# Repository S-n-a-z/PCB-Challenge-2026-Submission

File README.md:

# PCB Challenge 2026

My working layout for the [Fleming Society PCB Challenge](https://github.com/Fleming-Society/PCB-Challenge-2026).

This branch is not ready for submission. There are still **18 unconnected items**, along with two via-placement issues and symbol and footprint mismatches to resolve before the final check.

## Current layout

| Item | Result |
| --- | --- |
| Board outline | 66.7 × 67.2 mm |
| Bounding-box area | 4,482.24 mm² |
| Components | 164 |
| Copper layers | Four |
| Board thickness | 1.6 mm |
| Unconnected items | 18 |
| Other standard DRC errors | 0 |
| DRC warnings | 16 |
| Additional schematic-parity findings | 39 |

This checkpoint includes the manual routing progress and further data, enable and read-pointer connections. The remaining work is listed, with coordinates, in [Remaining connections](REMAINING_CONNECTIONS.md). No claim is made that this is ready for manufacture or a completed challenge entry.

The inner layers carry ground and 3V3 pours as well as some signal routes. The control routes on the ground layer stay outside the USB reference area. A separate check of the filled zone found no gaps beneath either main USB trace.

## Opening the project

Open `pcb_challenge_final.kicad_pro` in KiCad 10. The supplied custom footprints are included under `footprints/` and linked through `fp-lib-table`.

The schematic comes from the organisers' corrected files at commit [`8f8f4e2`](https://github.com/Fleming-Society/PCB-Challenge-2026/commit/8f8f4e241fe25e6dbe64b1d4abbda95879012cd6). The layout retains their footprint geometry, including the supplied ESP32 footprint that differs from the installed KiCad library.

## Checks and remaining work

The [DRC report](checks/drc.json) was generated with KiCad 10.0.7. It includes the open connections and the separate schematic-parity findings. The source has inconsistencies around the reset switch, unused symbol pins and USB shield numbering; these still need reviewing. The shield pads are named `SH` in the footprint and `S1` in the symbol.

The [layout audit](checks/layout-audit.json) checks via placement and the USB reference plane. Two existing vias on `b2` and `b3` overlap U10's courtyard; the `b2` via is also in a pad. Those still need moving. The check found no gaps beneath the main USB traces. The same-layer IC courtyard restriction still needs a full review.

The design rules use a 0.15 mm minimum track width, 0.12 mm clearance, 0.3 mm copper-to-edge clearance and 0.6/0.3 mm vias with a 0.15 mm annular ring. Zero other standard DRC errors does not mean the board is finished: open connections and the separate parity and challenge-rule findings remain.

The logic deduction is kept in the local form notes rather than this public repository. The [submission checklist](SUBMISSION_CHECKLIST.md) records what is still outstanding.

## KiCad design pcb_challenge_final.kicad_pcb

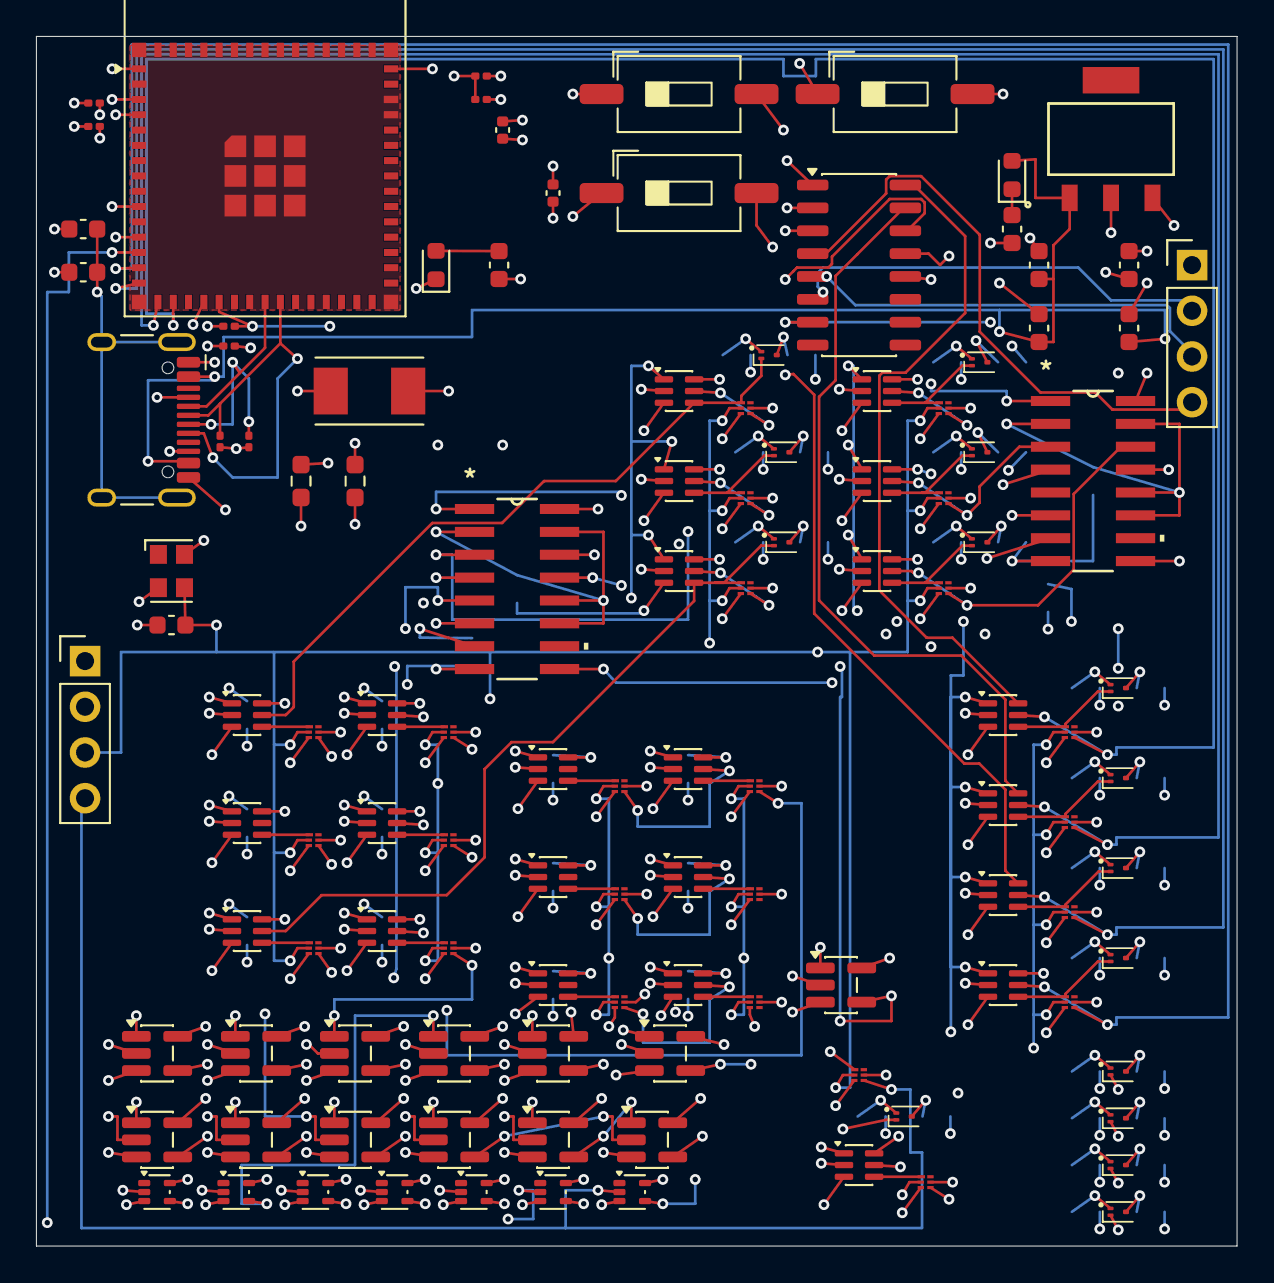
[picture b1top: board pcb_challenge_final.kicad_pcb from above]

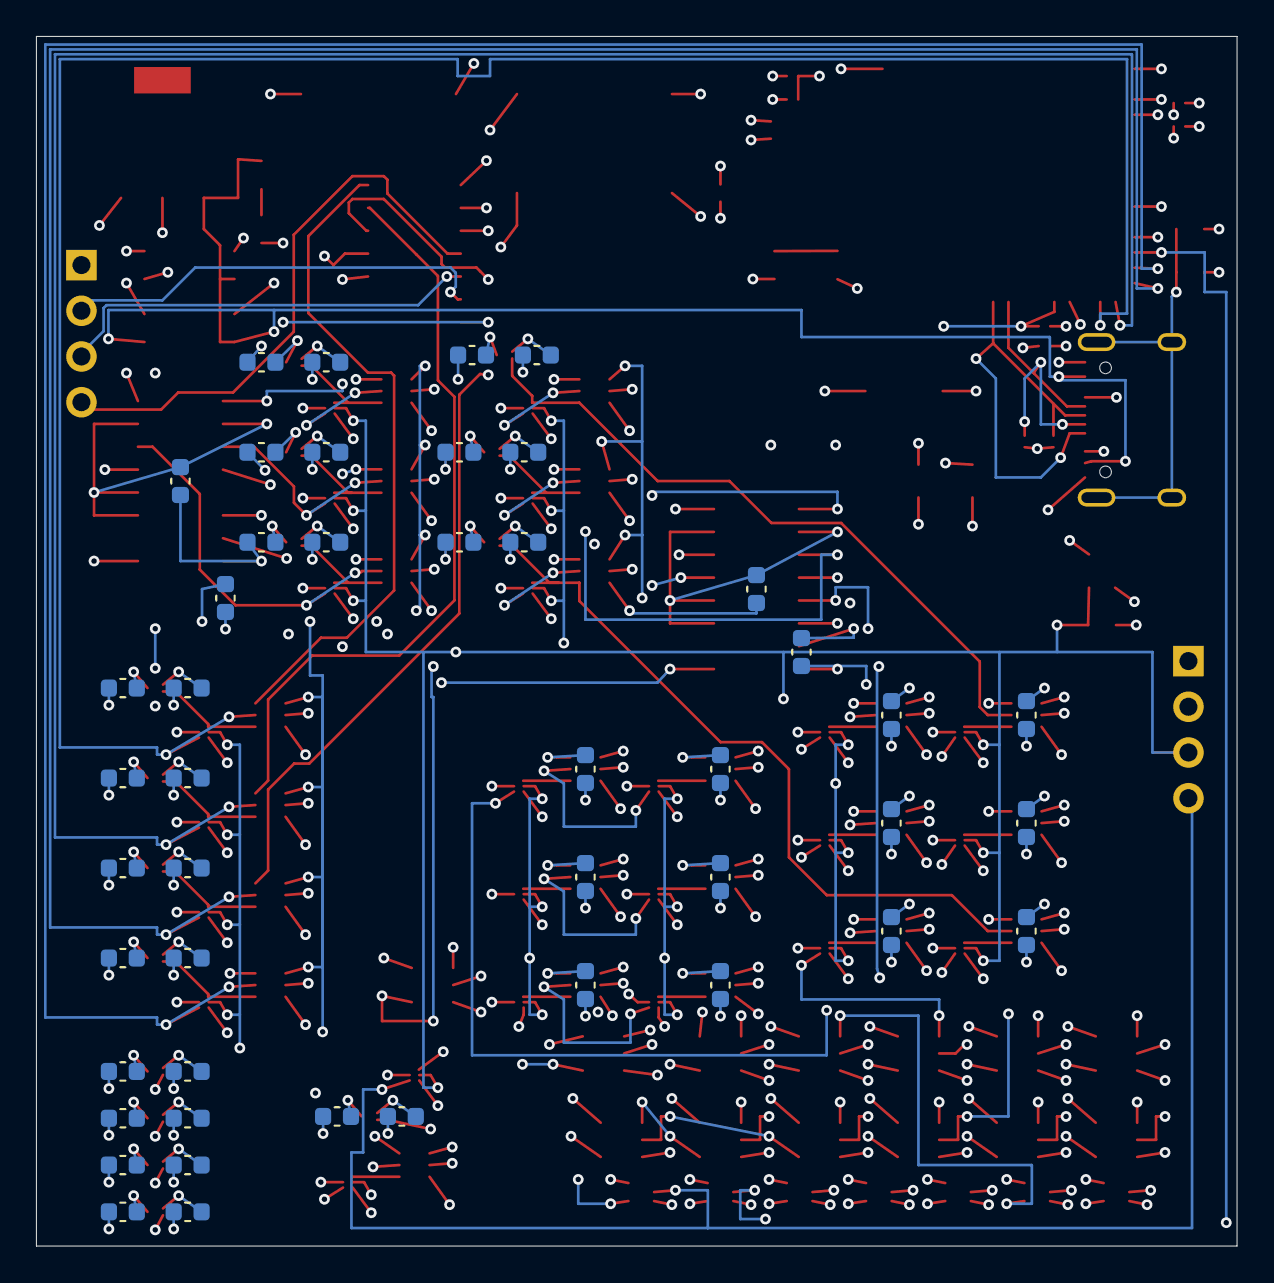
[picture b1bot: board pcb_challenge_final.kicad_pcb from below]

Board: 4 copper layers, 66.7 x 67.2 mm, 164 parts (46 on the bottom side), 134 nets.

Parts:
C1, C7: 22uF; C_0201_0603Metric
C2, C8: 0.1uF; C_0201_0603Metric
C3, C4: 12pF; C_0201_0603Metric
C5, C6: 22pF; C_0201_0603Metric
C9: 100nF; C_0402_1005Metric
C13, C14: 1uF; C_0603_1608Metric
C15, C20: 10uF; C_0603_1608Metric
D1: BLED; LED_0603_1608Metric
GREEN_LED1: LED; LED_0603_1608Metric
J3: USB_C_Receptacle_HCTL_HC-TYPE-C-16P-01A
J4, J5: Conn_01x04_Pin; PinHeader_1x04_P2.54mm_Vertical
Q15, Q16, Q17, Q18, Q19, Q20, Q21, Q22, Q23, Q24, Q25, Q26, Q27, Q28, Q29: Q_Dual_NPN_PNP_B1E2B2C2E1C1; SOT-1123
R1: 10k; C_0402_1005Metric
R3: 1k; C_0603_1608Metric
R4: 330; C_0603_1608Metric
R6, R24: 1M; C_0603_1608Metric
R7, R21, R22, R23, R25, R26, R27, R28, R29, R30, R31, R32, R33, R34, R35, R36, R37, R38, R39, R40, R41, R42, R43, R44, R45, R46, R47, R48, R49, R50, R51, R52, R53, R54, R55, R56, R57, R58, R59, R61, R62, R63, R64, R65, R66, R67, R68: 10k; C_0603_1608Metric
R15, R20: 5.1k; R_0603_1608Metric_Pad0.98x0.95mm_HandSolder
SW1, SW2, SW3: SW_Push; SW_DIP_SPSTx01_Slide_6.7x4.1mm_W8.61mm_P2.54mm_LowProfile
U1, U4, U5, U6, U7, U8, U17, U19, U20, U33, U34, U37, U38, U45, U46, U47, U48, U49, U50, U65, U66, U67, U68, U69: 74AUP1G80; XSON6_SOT1115_NEX
U3, U18, U52, U55, U56, U60: 74AHC1G86; SC-74A-5_1.55x2.9mm_P0.95mm
U9: TC1262-25; SOT-223_3MC_MCH
U10: NMUX1308BQ; SO-16_3.9x9.9mm_P1.27mm
U11, U12, U13, U14, U15, U16, U29, U30, U31, U32, U35, U36, U39, U40, U41, U42, U43, U44, U64, U70, U71, U72, U73: NMUX1308BQ; SOT-363_SC-70-6
U21, U23, U27, U51, U59, U62, U63: 74LV1T08GV; SC-74A-5_1.55x2.9mm_P0.95mm
U22, U28: CD74HC283M96; D16
U24, U26, U53, U54, U57, U58, U61: 74LVC1GU04DRL; SOT-553
U25: ESP32-S3-MINI-1; ESP32-S2-MINI-1
Y1: 32.768KHz; Crystal_SMD_Abracon_ABM7-2Pin_6.0x3.5mm
Y2: KC2520Z; Oscillator_SMD_Kyocera_KC2520Z-4Pin_2.5x2.0mm

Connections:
+3.3V: C1.1, C2.1, C14.1, R1.1, R3.1, U1.5 (VCC), U3.5 (VCC), U4.5 (VCC), U5.5 (VCC), U6.5 (VCC), U7.5 (VCC), U8.5 (VCC), U9.3 (VO), U10.1 (V_{CC}), U11.2 (V_{CC}), U12.2 (V_{CC}), U13.2 (V_{CC}), U14.2 (V_{CC}), U15.2 (V_{CC}), U16.2 (V_{CC}), U17.5 (VCC), U18.5 (VCC), U19.5 (VCC), U20.5 (VCC), U21.5 (VCC), U22.6 (B0), U22.16 (VCC), U23.5 (VCC), U24.5 (+), U25.3 (3V3), U26.5 (+), U27.5 (VCC), U28.6 (B0), U28.16 (VCC), U29.2 (V_{CC}), U30.2 (V_{CC}), U31.2 (V_{CC}), U32.2 (V_{CC}), U33.5 (VCC), U34.5 (VCC), U35.2 (V_{CC}), U36.2 (V_{CC}), U37.5 (VCC), U38.5 (VCC), U39.2 (V_{CC}), U40.2 (V_{CC}), U41.2 (V_{CC}), U42.2 (V_{CC}), U43.2 (V_{CC}), U44.2 (V_{CC}), U45.5 (VCC), U46.5 (VCC), U47.5 (VCC), U48.5 (VCC), U49.5 (VCC), U50.5 (VCC), U51.5 (VCC), U52.5 (VCC), U53.5 (+), U54.5 (+), U55.5 (VCC), U56.5 (VCC), U57.5 (+), U58.5 (+), U59.5 (VCC), U60.5 (VCC), U61.5 (+), U62.5 (VCC), U63.5 (VCC), U64.2 (V_{CC}), U64.6 (Y1), U65.5 (VCC), U66.5 (VCC), U67.5 (VCC), U68.5 (VCC), U69.5 (VCC), U70.2 (V_{CC}), U71.2 (V_{CC}), U72.2 (V_{CC}), U73.2 (V_{CC}), Y2.4 (VCC)
+5V: C13.1, C15.1, C20.1, GREEN_LED1.2 (A), J3.A4 (VBUS), J3.A9 (VBUS), J3.B4 (VBUS), J3.B9 (VBUS), U9.1 (VI)
???: J5.4, U1.4 (~Q), U26.2
COUT: U22.9 (COUT), U28.9 (COUT)
GND: C1.2, C2.2, C3.1, C4.1, C5.2, C6.2, C7.2, C8.2, C9.2, C13.2, C14.2, C15.2, C20.2, D1.1 (K), J3.A1 (GND), J3.A12 (GND), J3.B1 (GND), J3.B12 (GND), R4.1, R6.1, R7.1, R15.1, R20.2, R21.1, R22.1, R23.1, R24.1, R25.1, R26.1, R27.1, R28.1, R29.1, R30.1, R31.1, R32.1, R33.1, R34.1, R35.1, R36.1, R37.1, R38.1, R39.1, R40.1, R41.1, R42.1, R43.1, R44.1, R45.1, R46.1, R47.1, R48.1, R49.1, R50.1, R51.1, R52.1, R53.1, R54.1, R55.1, R56.1, R57.1, R58.1, R59.1, R61.1, R62.1, R63.1, R64.1, R65.1, R66.1, R67.1, R68.1, SW1.1, SW2.1, SW3.2, U1.3 (GND), U3.3 (GND), U4.3 (GND), U5.3 (GND), U6.3 (GND), U7.3 (GND), U8.3 (GND), U9.2 (GND), U10.2 (GND), U11.3 (GND), U12.3 (GND), U13.3 (GND), U14.3 (GND), U15.3 (GND), U16.3 (GND), U17.3 (GND), U18.3 (GND), U19.3 (GND), U20.3 (GND), U21.3 (GND), U22.8 (GND), U23.3 (GND), U24.3 (-), U25.1 (GND), U26.3 (-), U27.3 (GND), U28.8 (GND), U29.3 (GND), U30.3 (GND), U31.3 (GND), U32.3 (GND), U33.3 (GND), U34.3 (GND), U35.3 (GND), U36.3 (GND), U37.3 (GND), U38.3 (GND), U39.3 (GND), U40.3 (GND), U41.3 (GND), U42.3 (GND), U43.3 (GND), U44.3 (GND), U45.3 (GND), U46.3 (GND), U47.3 (GND), U48.3 (GND), U49.3 (GND), U50.3 (GND), U51.3 (GND), U52.3 (GND), U53.3 (-), U54.3 (-), U55.3 (GND), U56.3 (GND), U57.3 (-), U58.3 (-), U59.3 (GND), U60.3 (GND), U61.3 (-), U62.3 (GND), U63.3 (GND), U64.3 (GND), U65.3 (GND), U66.3 (GND), U67.3 (GND), U68.3 (GND), U69.3 (GND), U70.3 (GND), U71.3 (GND), U72.3 (GND), U73.3 (GND), Y2.2 (GND)
IO6: U6.2 (C), U7.2 (C), U8.2 (C), U25.10 (IO6), U45.2 (C), U46.2 (C), U47.2 (C), U48.2 (C), U49.2 (C), U50.2 (C), U65.2 (C), U66.2 (C), U67.2 (C), U68.2 (C), U69.2 (C)
IO7: U21.2 (A), U25.11 (IO7)
IO8: Q18.1 (B1), Q19.1 (B1), Q20.1 (B1), Q24.1 (B1), Q25.1 (B1), Q26.1 (B1), Q27.1 (B1), R35.2, R37.2, R39.2, R61.2, R63.2, R65.2, R67.2, U25.12 (IO8), U39.1 (S0), U40.1 (S0), U41.1 (S0), U42.1 (S0), U43.1 (S0), U44.1 (S0), U64.1 (S0)
IO9: U24.2, U25.13 (IO9), U65.4 (~Q)
IO10: U25.14 (IO10), U69.4 (~Q), U73.5 (Y0)
IO11: U25.15 (IO11), U68.4 (~Q), U70.5 (Y0)
IO12: U25.16 (IO12), U67.4 (~Q), U71.5 (Y0)
IO13: U25.17 (IO13), U66.4 (~Q), U72.5 (Y0)
unnamed: D1.2 (A), R3.2
unnamed: GREEN_LED1.1 (K), R4.2
unnamed: J3.A5 (CC1), R20.1
unnamed: J3.B5 (CC2), R15.2
unnamed: J3.SH, R6.2, R24.2
unnamed: Q15.3 (E1), R30.2
unnamed: Q16.2 (C1), U1.1 (D), U27.4 (Y)
unnamed: Q16.3 (E1), R32.2
unnamed: Q17.3 (E1), R28.2
unnamed: Q18.3 (E1), R40.2
unnamed: Q19.3 (E1), R38.2
unnamed: Q20.3 (E1), R36.2
unnamed: Q21.3 (E1), R44.2
unnamed: Q22.3 (E1), R45.2
unnamed: Q23.3 (E1), R46.2
unnamed: Q24.2 (C1), U66.1 (D), U72.4 (Out)
unnamed: Q24.3 (E1), R62.2
unnamed: Q25.2 (C1), U67.1 (D), U71.4 (Out)
unnamed: Q25.3 (E1), R64.2
unnamed: Q26.2 (C1), U68.1 (D), U70.4 (Out)
unnamed: Q26.3 (E1), R66.2
unnamed: Q27.2 (C1), U69.1 (D), U73.4 (Out)
unnamed: Q27.3 (E1), R68.2
unnamed: Q28.3 (E1), R26.2
unnamed: Q29.3 (E1), R22.2
unnamed: U18.4, U54.2
unnamed: U21.1 (B), U24.4
unnamed: R33.2, U22.2 (B1), U22.11 (B3), U22.12 (A3), U22.15 (B2)
unnamed: R25.2, U22.7 (CIN)
unnamed: U23.1 (B), U26.4
unnamed: C7.1, C8.1, R1.2, SW3.1, U25.45 (EN)
unnamed: U25.2 (GND), U25.42 (GND), U25.43 (GND), U25.46 (GND), U25.47 (GND), U25.48 (GND), U25.49 (GND), U25.50 (GND), U25.51 (GND), U25.52 (GND), U25.53 (GND), U25.54 (GND), U25.55 (GND), U25.56 (GND), U25.57 (GND), U25.58 (GND), U25.59 (GND), U25.60 (GND), U25.61 (GND), U25.62 (GND), U25.63 (GND), U25.64 (GND), U25.65 (GND)
unnamed: SW1.2, U25.4 (IO0)
unnamed: C3.2, U25.19 (IO15), Y1.2
unnamed: C4.2, U25.20 (IO16), Y1.1
unnamed: U3.4, U27.2 (A)
unnamed: U27.1 (B), U51.4 (Y)
unnamed: R47.2, U28.2 (B1), U28.11 (B3), U28.12 (A3), U28.15 (B2)
unnamed: R34.2, U28.7 (CIN)
unnamed: U4.1 (D), U29.4 (Out)
unnamed: R48.2, U29.6 (Y1)
unnamed: U5.1 (D), U30.4 (Out)
unnamed: U4.4 (~Q), U30.5 (Y0)
unnamed: R49.2, U30.6 (Y1)
unnamed: U31.4 (Out), U33.1 (D)
unnamed: R50.2, U31.6 (Y1)
unnamed: U32.4 (Out), U34.1 (D)
unnamed: U32.5 (Y0), U33.4 (~Q)
unnamed: R51.2, U32.6 (Y1)
unnamed: U35.4 (Out), U37.1 (D)
unnamed: R52.2, U35.6 (Y1)
unnamed: U36.4 (Out), U38.1 (D)
unnamed: U36.5 (Y0), U37.4 (~Q)
unnamed: R53.2, U36.6 (Y1)
unnamed: U39.4 (Out), U45.1 (D)
unnamed: R54.2, U39.6 (Y1)
unnamed: U40.4 (Out), U46.1 (D)
unnamed: R55.2, U40.6 (Y1)
unnamed: U41.4 (Out), U47.1 (D)
unnamed: R56.2, U41.6 (Y1)
unnamed: U42.4 (Out), U48.1 (D)
unnamed: U42.5 (Y0), U45.4 (~Q)
unnamed: R57.2, U42.6 (Y1)
unnamed: U43.4 (Out), U49.1 (D)
unnamed: U43.5 (Y0), U46.4 (~Q)
unnamed: R58.2, U43.6 (Y1)
unnamed: U44.4 (Out), U50.1 (D)
unnamed: U44.5 (Y0), U47.4 (~Q)
unnamed: R59.2, U44.6 (Y1)
unnamed: U51.2 (A), U54.4
unnamed: U51.1 (B), U53.4
unnamed: U52.4, U53.2
unnamed: U55.4, U57.2
unnamed: U56.4, U58.2
unnamed: U57.4, U59.2 (A)
unnamed: U58.4, U59.1 (B), U62.2 (A)
unnamed: U59.4 (Y), U63.2 (A)
unnamed: U60.4, U61.2
unnamed: U61.4, U62.1 (B)
unnamed: U62.4 (Y), U63.1 (B)
unnamed: U63.4 (Y), U64.5 (Y0)
unnamed: U64.4 (Out), U65.1 (D)
R_en: U10.12 (EN), U14.1 (S0), U15.1 (S0), U16.1 (S0), U23.4 (Y)
USB_D+: C5.1, J3.A6 (D+), J3.B6 (D+), U25.24 (USB_D+)
USB_D-: C6.1, J3.A7 (D-), J3.B7 (D-), U25.23 (USB_D-)
b1: J4.4, Q29.2 (C1), U10.4 (in1)
b2: J4.3, Q28.2 (C1), U10.5 (in2)
b3: J4.2, Q17.2 (C1), U10.6 (in3)
b4: J4.1, Q15.2 (C1), U10.7 (in4)
clk: J5.3, R7.2, U1.2 (C), U4.2 (C), U5.2 (C), U10.3 (clk), U17.2 (C), U19.2 (C), U20.2 (C), U33.2 (C), U34.2 (C), U37.2 (C), U38.2 (C), Y2.3 (CLK)
en: J5.1, U23.2 (A)
out_1: U10.13 (o1), U73.6 (Y1)
out_2: U10.14 (o2), U70.6 (Y1)
out_3: U10.15 (o3), U71.6 (Y1)
out_4: U10.16 (o4), U72.6 (Y1)
r_en: U11.1 (S0), U12.1 (S0), U13.1 (S0), U21.4 (Y), U70.1 (S0), U71.1 (S0), U72.1 (S0), U73.1 (S0)
rc1: U7.4 (~Q), U10.10 (in1), U12.5 (Y0), U22.5 (A0), U60.1
rc2: U6.4 (~Q), U10.11 (in2), U11.5 (Y0), U22.3 (A1), U56.2
rc3: U8.4 (~Q), U13.5 (Y0), U22.14 (A2), U55.2
reg1: U5.4 (~Q), U18.1
reg2: U34.4 (~Q), U52.1
reg3: U3.1, U38.4 (~Q)
rs0: U12.6 (Y1), U22.4 (S0)
rs1: U11.6 (Y1), U22.1 (S1)
rs2: U13.6 (Y1), U22.13 (S2)
rst: C9.1, J5.2, Q15.1 (B1), Q16.1 (B1), Q17.1 (B1), Q21.1 (B1), Q22.1 (B1), Q23.1 (B1), Q28.1 (B1), Q29.1 (B1), R21.2, R23.2, R27.2, R29.2, R31.2, R41.2, R42.2, R43.2, SW2.2, U29.1 (S0), U30.1 (S0), U31.1 (S0), U32.1 (S0), U35.1 (S0), U36.1 (S0)
rw1: Q20.2 (C1), U7.1 (D), U12.4 (Out), U29.5 (Y0)
rw2: Q19.2 (C1), U6.1 (D), U11.4 (Out), U31.5 (Y0)
rw3: Q18.2 (C1), U8.1 (D), U13.4 (Out), U35.5 (Y0)
wc1: U10.8 (in1), U15.5 (Y0), U18.2, U20.4 (~Q), U28.5 (A0)
wc2: U10.9 (in2), U14.5 (Y0), U19.4 (~Q), U28.3 (A1), U52.2
wc3: U3.2, U16.5 (Y0), U17.4 (~Q), U28.14 (A2)
wir1: U48.4 (~Q), U60.2
wir2: U49.4 (~Q), U56.1
wir3: U50.4 (~Q), U55.1
wr1: Q23.2 (C1), U15.4 (Out), U20.1 (D), U39.5 (Y0)
wr2: Q22.2 (C1), U14.4 (Out), U19.1 (D), U40.5 (Y0)
wr3: Q21.2 (C1), U16.4 (Out), U17.1 (D), U41.5 (Y0)
ws0: U15.6 (Y1), U28.4 (S0)
ws1: U14.6 (Y1), U28.1 (S1)
ws2: U16.6 (Y1), U28.13 (S2)
